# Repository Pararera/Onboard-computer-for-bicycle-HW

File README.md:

# ONBOARD COMPUTER FOR BICYCLE - HARDWARE

<a href="https://github.com/Pararera/Onboard-computer-for-bicycle-SW" title="Repo for software development." target="_blank">Software repo</a>
<br/>
<a href="https://create.arduino.cc/projecthub/Pararera/onboard-computer-for-bicycle-023f25" title="Arduino Project Hub" target="_blank">Link to the project page</a>

The project is in WIP stage. New stuff soon.

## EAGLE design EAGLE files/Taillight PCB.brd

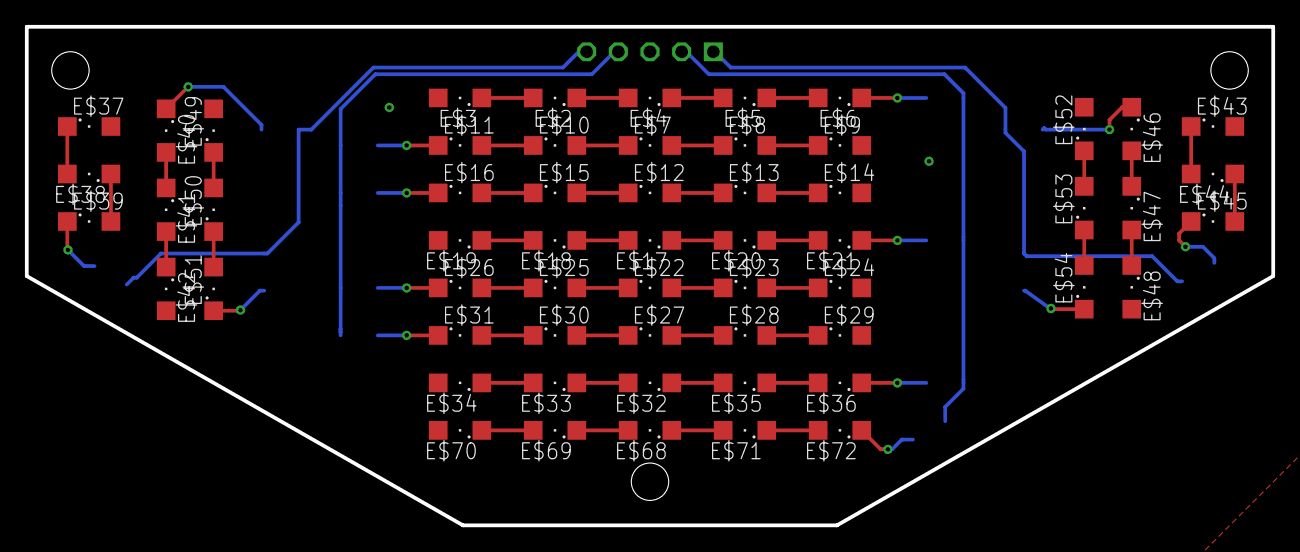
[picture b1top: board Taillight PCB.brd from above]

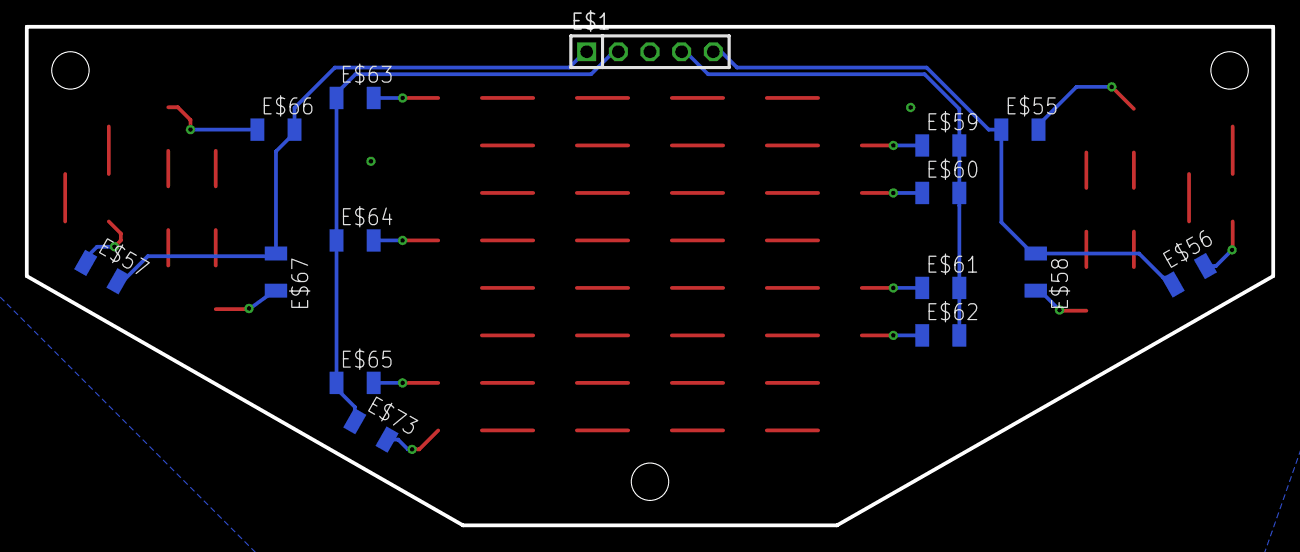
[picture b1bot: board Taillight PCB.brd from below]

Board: 2 copper layers, 100.0 x 40.0 mm, 73 parts (15 on the bottom side), 63 nets.

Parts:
E$1: 1X05
E$2, E$3, E$4, E$5, E$6, E$7, E$8, E$9, E$10, E$11, E$12, E$13, E$14, E$15, E$16, E$17, E$18, E$19, E$20, E$21, E$22, E$23, E$24, E$25, E$26, E$27, E$28, E$29, E$30, E$31, E$32, E$33, E$34, E$35, E$36, E$37, E$38, E$39, E$40, E$41, E$42, E$43, E$44, E$45, E$46, E$47, E$48, E$49, E$50, E$51, E$52, E$53, E$54, E$68, E$69, E$70, E$71, E$72: SML1206
E$55, E$56, E$57, E$58, E$59, E$60, E$61, E$62, E$63, E$64, E$65, E$66, E$67, E$73: R1206

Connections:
S$1: E$2.A, E$3.C
S$2: E$2.C, E$4.A
S$3: E$4.C, E$5.A
S$4: E$5.C, E$6.A
S$5: E$6.C, E$63.2
S$6: E$20.C, E$21.A
S$7: E$17.C, E$20.A
S$8: E$17.A, E$18.C
S$9: E$18.A, E$19.C
S$10: E$33.A, E$34.C
S$11: E$32.A, E$33.C
S$12: E$32.C, E$35.A
S$13: E$35.C, E$36.A
S$14: E$36.C, E$65.2
S$15: E$21.C, E$64.2
S$16: E$1.2, E$63.1, E$64.1, E$65.1, E$73.1
S$17: E$52.C, E$53.A
S$18: E$53.C, E$54.A
S$19: E$54.C, E$67.2
S$20: E$46.A, E$47.C
S$21: E$47.A, E$48.C
S$22: E$43.C, E$44.A
S$23: E$44.C, E$45.A
S$24: E$1.1, E$57.2, E$66.2, E$67.1
S$25: E$46.C, E$66.1
S$26: E$45.C, E$57.1
S$27: E$8.A, E$9.C
S$28: E$7.A, E$8.C
S$29: E$7.C, E$10.A
S$30: E$10.C, E$11.A
S$31: E$11.C, E$59.1
S$32: E$69.A, E$70.C
S$33: E$26.C, E$61.1
S$34: E$25.C, E$26.A
S$35: E$22.C, E$25.A
S$36: E$22.A, E$23.C
S$37: E$23.A, E$24.C
S$38: E$28.A, E$29.C
S$39: E$27.A, E$28.C
S$40: E$27.C, E$30.A
S$41: E$30.C, E$31.A
S$42: E$31.C, E$62.1
S$43: E$13.A, E$14.C
S$44: E$12.A, E$13.C
S$45: E$12.C, E$15.A
S$46: E$15.C, E$16.A
S$47: E$16.C, E$60.1
S$49: E$37.C, E$38.A
S$50: E$38.C, E$39.A
S$51: E$39.C, E$56.2
S$52: E$41.A, E$42.C
S$53: E$40.A, E$41.C
S$54: E$49.C, E$50.A
S$55: E$50.C, E$51.A
S$56: E$51.C, E$58.2
S$57: E$40.C, E$55.2
S$58: E$1.5, E$55.1, E$56.1, E$58.1
S$59: E$68.A, E$69.C
S$60: E$68.C, E$71.A
S$61: E$1.4, E$59.2, E$60.2, E$61.2, E$62.2
S$62: E$71.C, E$72.A
S$63: E$72.C, E$73.2
VCC: E$1.3, E$3.A, E$9.A, E$14.A, E$19.A, E$24.A, E$29.A, E$34.A, E$37.A, E$42.A, E$43.A, E$48.A, E$49.A, E$52.A, E$70.A

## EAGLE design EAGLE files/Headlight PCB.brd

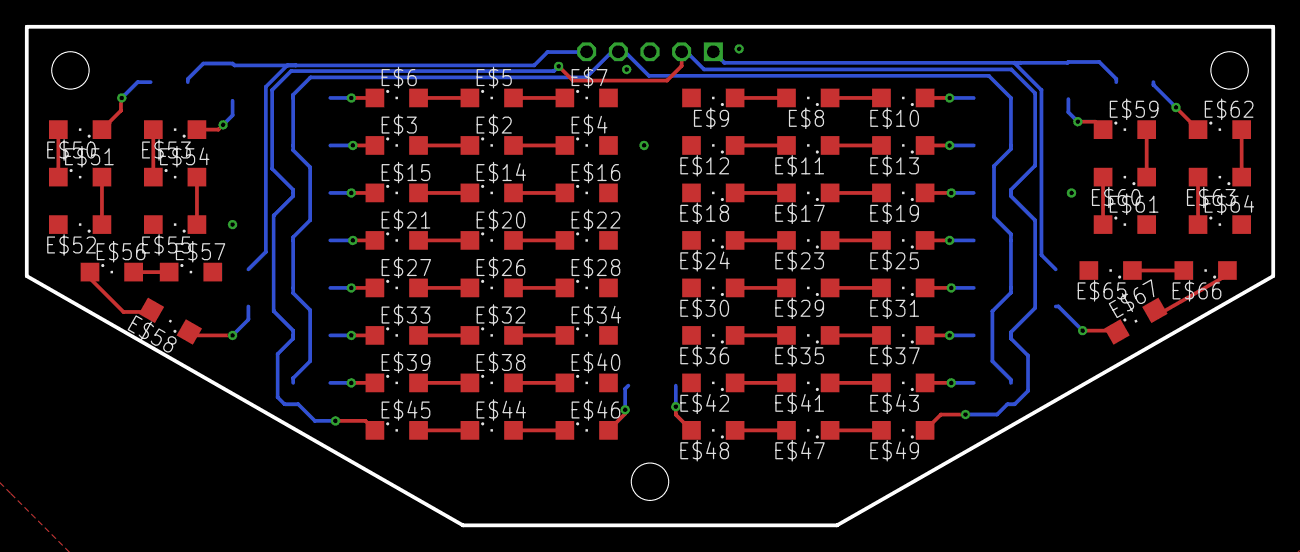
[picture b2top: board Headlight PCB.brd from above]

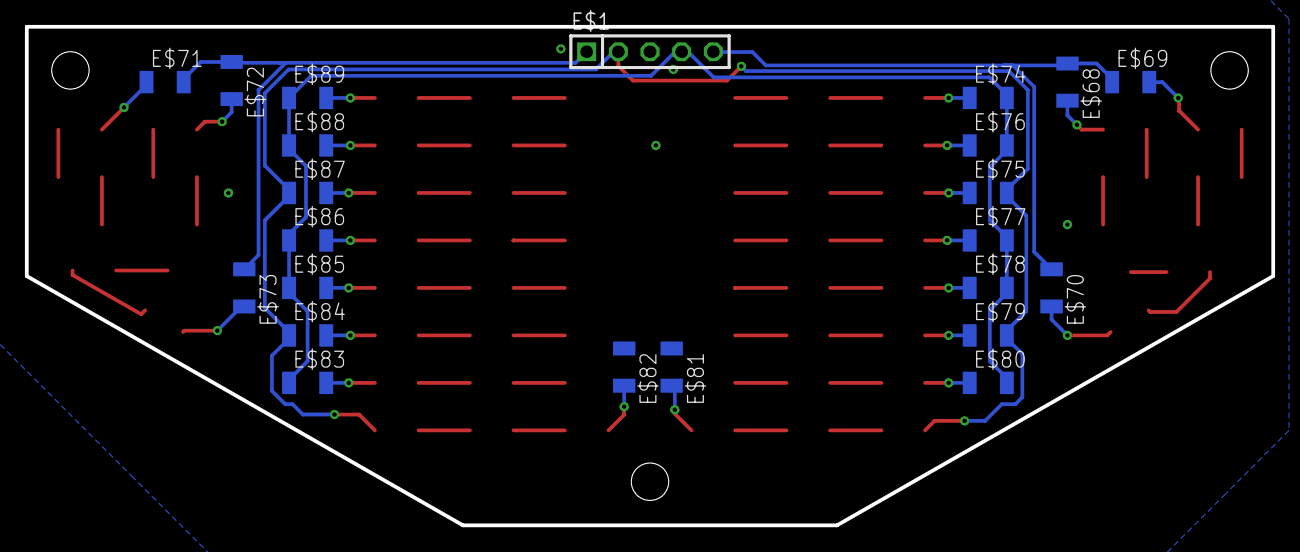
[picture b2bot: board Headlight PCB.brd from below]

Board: 2 copper layers, 100.0 x 40.0 mm, 89 parts (23 on the bottom side), 71 nets.

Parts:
E$1: 1X05
E$2, E$3, E$4, E$5, E$6, E$7, E$8, E$9, E$10, E$11, E$12, E$13, E$14, E$15, E$16, E$17, E$18, E$19, E$20, E$21, E$22, E$23, E$24, E$25, E$26, E$27, E$28, E$29, E$30, E$31, E$32, E$33, E$34, E$35, E$36, E$37, E$38, E$39, E$40, E$41, E$42, E$43, E$44, E$45, E$46, E$47, E$48, E$49, E$50, E$51, E$52, E$53, E$54, E$55, E$56, E$57, E$58, E$59, E$60, E$61, E$62, E$63, E$64, E$65, E$66, E$67: SML1206
E$68, E$69, E$70, E$71, E$72, E$73, E$74, E$75, E$76, E$77, E$78, E$79, E$80, E$81, E$82, E$83, E$84, E$85, E$86, E$87, E$88, E$89: R1206

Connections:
S$1: E$51.A, E$52.C
S$2: E$50.A, E$51.C
S$3: E$50.C, E$69.2
S$5: E$54.A, E$55.C
S$6: E$53.A, E$54.C
S$7: E$56.A, E$57.C
S$8: E$56.C, E$58.A
S$9: E$58.C, E$70.2
S$10: E$53.C, E$68.2
S$11: E$5.A, E$7.C
S$12: E$5.C, E$6.A
S$13: E$2.A, E$4.C
S$14: E$2.C, E$3.A
S$15: E$14.C, E$15.A
S$16: E$14.A, E$16.C
S$17: E$20.A, E$22.C
S$18: E$20.C, E$21.A
S$19: E$26.C, E$27.A
S$20: E$26.A, E$28.C
S$21: E$32.A, E$34.C
S$22: E$32.C, E$33.A
S$23: E$38.C, E$39.A
S$24: E$38.A, E$40.C
S$25: E$44.A, E$46.C
S$26: E$44.C, E$45.A
S$27: E$47.A, E$48.C
S$28: E$41.A, E$42.C
S$29: E$35.A, E$36.C
S$30: E$29.A, E$30.C
S$31: E$23.A, E$24.C
S$32: E$17.A, E$18.C
S$33: E$11.A, E$12.C
S$34: E$8.A, E$9.C
S$35: E$8.C, E$10.A
S$36: E$11.C, E$13.A
S$37: E$17.C, E$19.A
S$38: E$23.C, E$25.A
S$39: E$29.C, E$31.A
S$40: E$35.C, E$37.A
S$41: E$41.C, E$43.A
S$42: E$47.C, E$49.A
S$43: E$6.C, E$74.1
S$44: E$3.C, E$76.1
S$45: E$15.C, E$75.1
S$46: E$21.C, E$77.1
S$47: E$27.C, E$78.1
S$49: E$33.C, E$79.1
S$50: E$39.C, E$80.1
S$51: E$46.A, E$81.2
S$52: E$48.A, E$82.2
S$53: E$1.1, E$71.2, E$72.1, E$73.1
S$54: E$63.A, E$64.C
S$55: E$10.C, E$89.2
S$56: E$13.C, E$88.2
S$57: E$19.C, E$87.2
S$58: E$25.C, E$86.2
S$59: E$31.C, E$85.2
S$60: E$37.C, E$84.2
S$61: E$43.C, E$83.2
S$62: E$62.A, E$63.C
S$63: E$1.2, E$45.C, E$49.C, E$75.2, E$79.2, E$84.1, E$87.1
S$64: E$62.C, E$71.1
S$66: E$59.C, E$72.2
S$67: E$59.A, E$60.C
S$68: E$60.A, E$61.C
S$69: E$65.C, E$66.A
S$70: E$66.C, E$67.A
S$71: E$67.C, E$73.2
S$72: E$1.5, E$68.1, E$69.1, E$70.1
S$76: E$1.4, E$74.2, E$76.2, E$77.2, E$78.2, E$80.2, E$83.1, E$85.1, E$86.1, E$88.1, E$89.1
VCC: E$1.3, E$4.A, E$7.A, E$9.A, E$12.A, E$16.A, E$18.A, E$22.A, E$24.A, E$28.A, E$30.A, E$34.A, E$36.A, E$40.A, E$42.A, E$52.A, E$55.A, E$57.A, E$61.A, E$64.A, E$65.A, E$81.1, E$82.1

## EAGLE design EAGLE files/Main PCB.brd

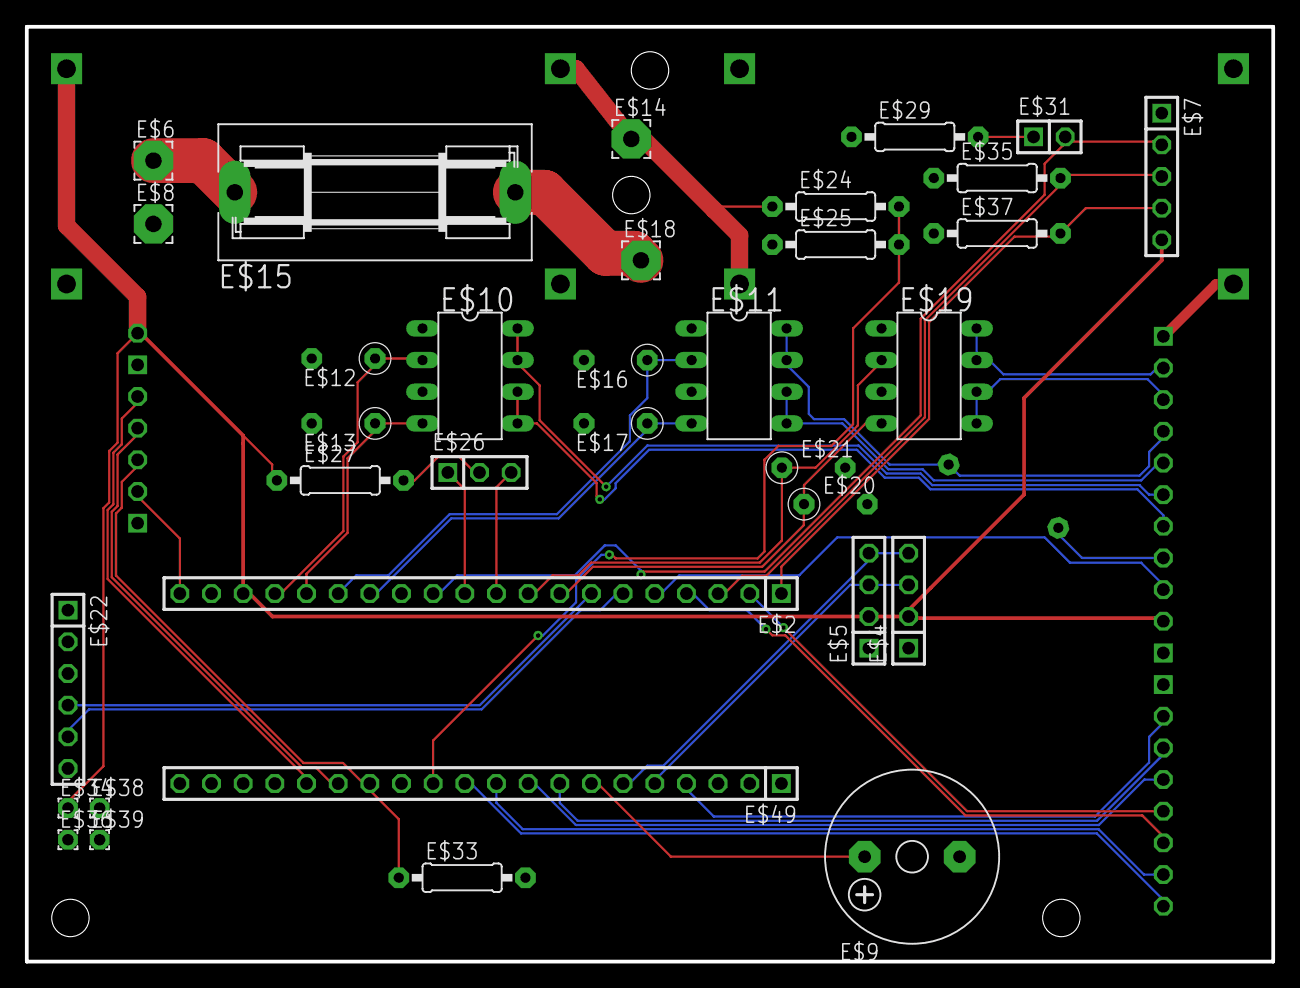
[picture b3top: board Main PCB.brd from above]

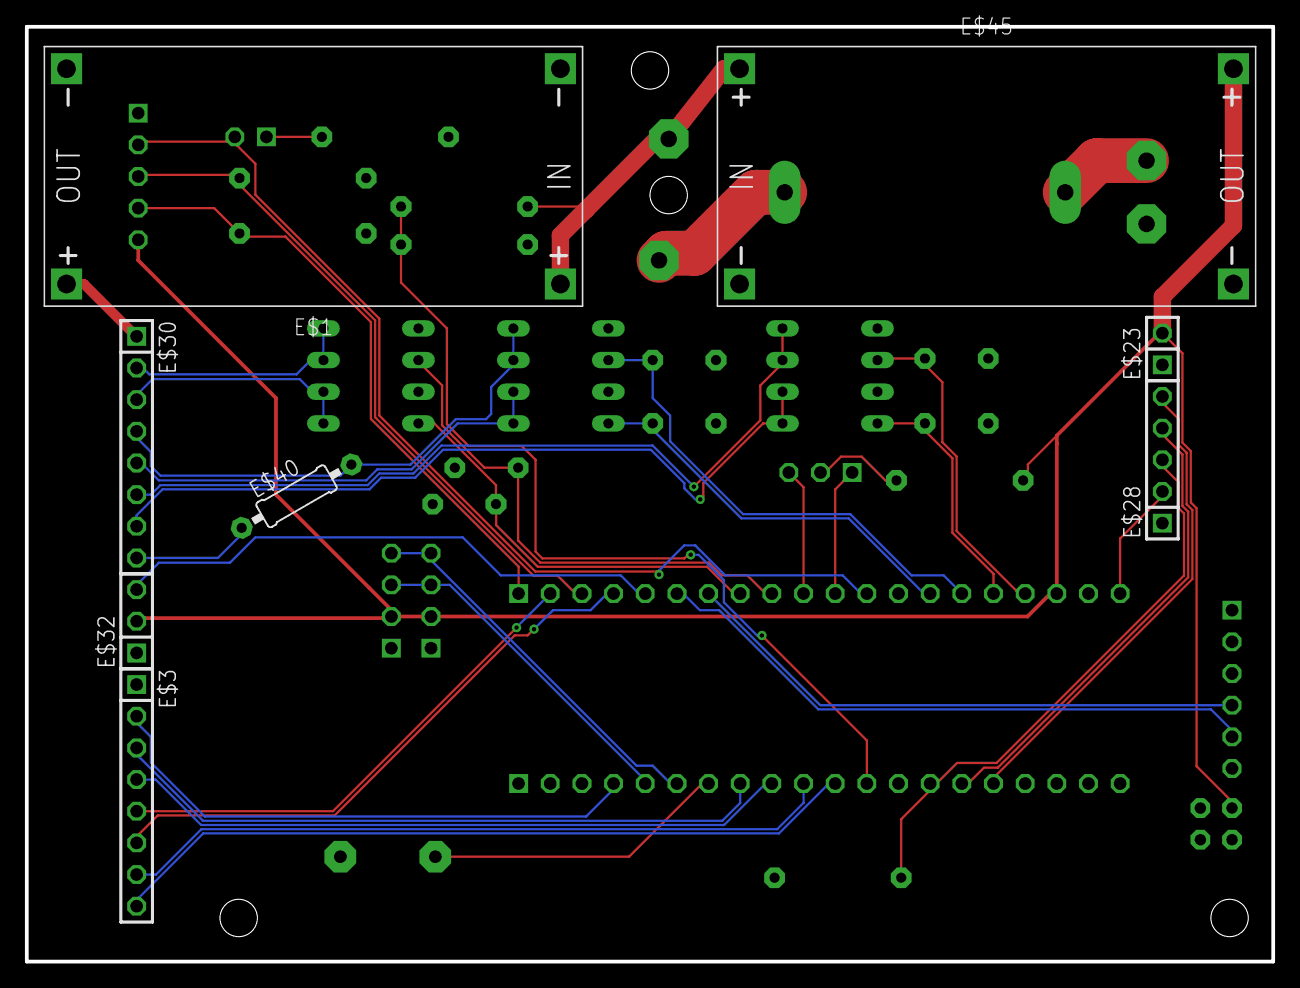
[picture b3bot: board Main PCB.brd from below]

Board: 2 copper layers, 100.0 x 75.0 mm, 42 parts (8 on the bottom side), 44 nets.

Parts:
E$1, E$45: DC-DC-STEP-DOWN-LM2596
E$2, E$49: 1X20
E$3, E$30: 1X08
E$4, E$5: 1X04
E$6, E$8, E$14, E$18: 3,17/1,3
E$7, E$28: 1X05
E$9: F/CM12P
E$10, E$11, E$19: DIL8
E$12, E$13, E$16, E$17, E$20, E$21: 0207/5V
E$15: SH22,5A
E$22: 1X06
E$23, E$31: 1X02
E$24, E$25, E$27, E$29, E$33, E$35, E$37, E$40: 0207/10
E$26, E$32: 1X03
E$34, E$36, E$38, E$39: 1,6/0,9

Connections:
GND: E$1.IN-, E$1.OUT-, E$2.19, E$3.1, E$4.1, E$5.1, E$7.1, E$8.1, E$9.-, E$10.1, E$10.3, E$11.1, E$11.3, E$12.2, E$13.2, E$16.2, E$17.2, E$19.1, E$19.3, E$20.2, E$21.2, E$22.1, E$23.1, E$25.1, E$28.1, E$29.1, E$32.1, E$33.2, E$35.1, E$36.1, E$37.1, E$45.IN-, E$45.OUT-, E$49.1, E$49.2
S$1: E$6.1, E$15.1
S$2: E$15.2, E$18.1
S$3: E$24.2, E$25.2, E$49.12
S$4: E$2.5, E$32.3
S$5: E$2.18, E$4.2, E$5.2, E$7.5, E$23.2, E$27.1, E$32.2, E$34.1, E$45.OUT+
S$6: E$1.OUT+, E$30.1
S$7: E$2.20, E$28.2
S$8: E$9.+, E$49.7
S$9: E$4.3, E$5.3, E$49.5
S$10: E$4.4, E$5.4, E$49.6
S$11: E$30.8, E$40.1
S$12: E$26.2, E$27.2
S$13: E$2.7, E$22.4
S$14: E$2.6, E$22.5
S$15: E$3.8, E$49.11
S$16: E$3.7, E$49.10
S$17: E$2.2, E$3.5
S$18: E$2.4, E$3.6
S$19: E$3.4, E$49.9
S$20: E$3.3, E$49.8
S$21: E$3.2, E$49.4
S$22: E$2.11, E$26.1
S$23: E$2.10, E$26.3
S$24: E$2.1, E$7.4, E$37.2
S$25: E$2.17, E$10.2, E$12.1
S$26: E$28.5, E$49.16
S$27: E$28.4, E$49.15
S$28: E$28.3, E$33.1, E$49.14
S$30: E$2.3, E$7.3, E$35.2
S$31: E$11.7, E$11.8, E$30.4, E$40.2
S$32: E$1.IN+, E$14.1, E$24.1, E$45.IN+
S$34: E$29.2, E$31.1
S$35: E$2.16, E$10.4, E$13.1
S$36: E$2.15, E$11.2, E$16.1
S$37: E$2.14, E$11.4, E$17.1
S$38: E$11.5, E$11.6, E$30.5
S$39: E$2.8, E$19.4, E$20.1
S$40: E$2.9, E$19.2, E$21.1
S$41: E$19.7, E$19.8, E$30.2
S$42: E$19.5, E$19.6, E$30.3
S$43: E$10.7, E$10.8, E$30.6
S$44: E$10.5, E$10.6, E$30.7
S$45: E$2.12, E$7.2, E$31.2

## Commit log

2020-07-04 First commit.

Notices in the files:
parts and their libraries:
diy-modules: Released under the Creative Commons Attribution 4.0 International License: http://creativecommons.org/licenses/by/4.0
